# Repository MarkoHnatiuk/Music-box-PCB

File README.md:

# Music box PCB
First time making PCBs in order to learn how it is done. I've decided to make a PCB for a circuit I used to built an electronic music box. 
During the project I learned how to create custom symbols and footprints, and how to, in the end, transfrom schematics into a PCB board that fits the capabilities of a manufacturer. 
Since it was my first PCB project, I went with a simple schematic, to focus on the basics.

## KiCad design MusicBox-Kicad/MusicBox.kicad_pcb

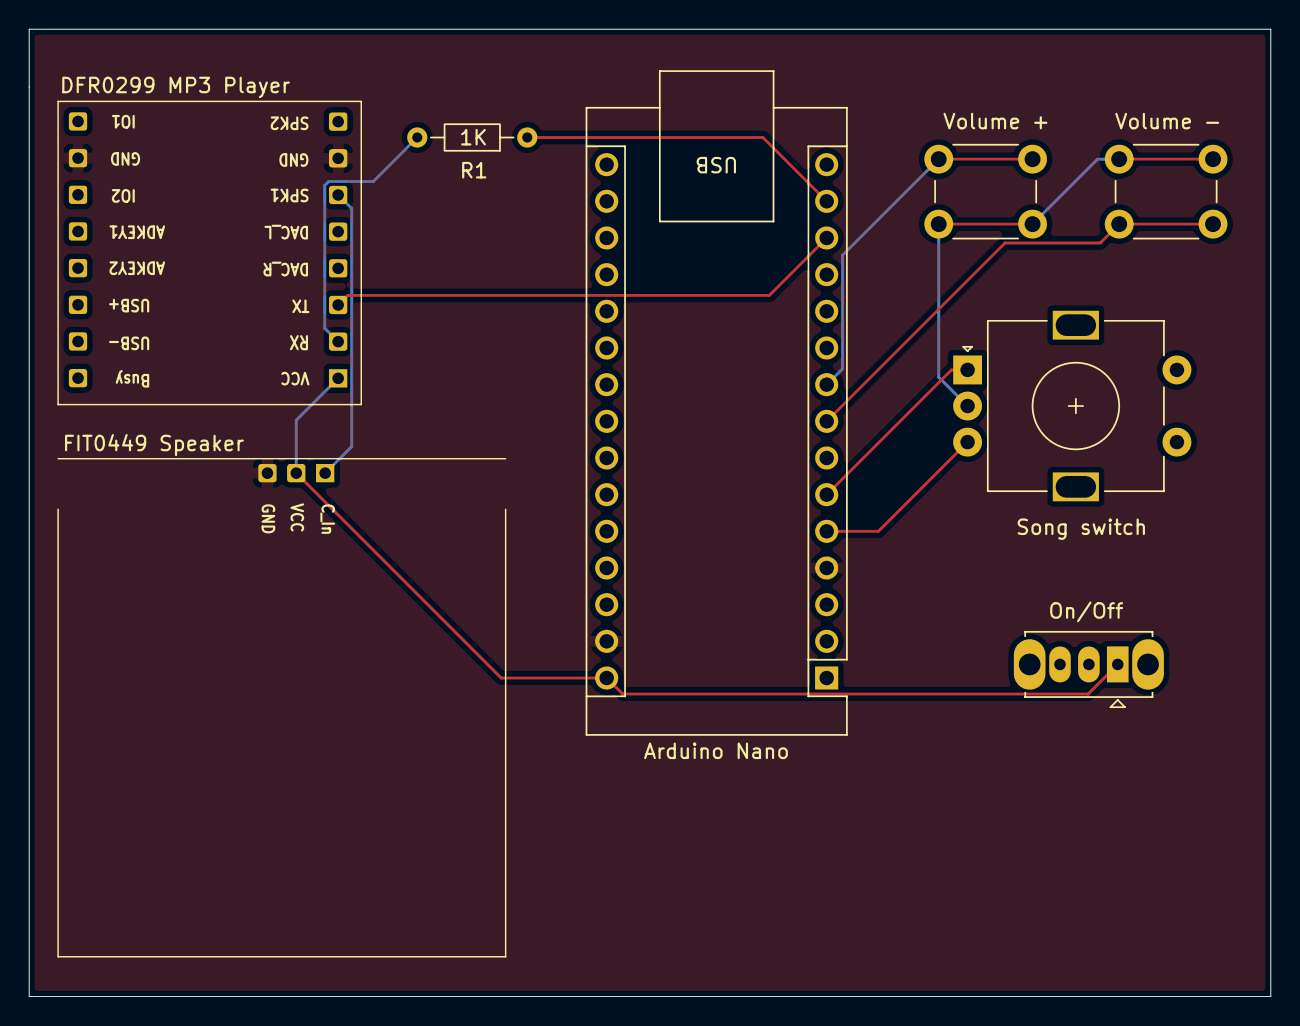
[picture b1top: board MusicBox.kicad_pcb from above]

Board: 2 copper layers, 86.0 x 67.0 mm, 8 parts (0 on the bottom side), 11 nets.

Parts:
Arduino Nano: Arduino_Nano_v3.x; Arduino_Nano
DFR0299 MP3 Player: DFR0299
FIT0449 Speaker: Speaker; RFSpeaker
On/Off: SW_SPDT; SW_Slide_SPDT_Straight_CK_OS102011MS2Q
R1: 1K; R_Axial_DIN0204_L3.6mm_D1.6mm_P7.62mm_Horizontal
Song switch: RotaryEncoder; RotaryEncoder_Alps_EC11E-Switch_Vertical_H20mm
Volume +: SW_Push; SW_PUSH_6mm
Volume -: SW_Push; SW_PUSH_6mm

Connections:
GND: Arduino Nano.4 (GND), Arduino Nano.29 (GND), DFR0299 MP3 Player.7 (GND), DFR0299 MP3 Player.10 (GND), FIT0449 Speaker.3 (GND)
unnamed: Arduino Nano.5 (D2), Song switch.B
unnamed: Arduino Nano.6 (D3), Song switch.A
unnamed: Arduino Nano.8 (D5), Volume -.2
unnamed: Arduino Nano.9 (D6), Volume +.1
unnamed: Arduino Nano.13 (D10), DFR0299 MP3 Player.3 (TX)
unnamed: Arduino Nano.14 (D11), R1.1
unnamed: Arduino Nano.30 (VIN), DFR0299 MP3 Player.1 (VCC), FIT0449 Speaker.2 (VCC), On/Off.1 (A)
unnamed: Song switch.C, Volume +.2, Volume -.1
unnamed: DFR0299 MP3 Player.2 (RX), R1.2
unnamed: DFR0299 MP3 Player.6 (SPK1), FIT0449 Speaker.1 (Control_IN)
